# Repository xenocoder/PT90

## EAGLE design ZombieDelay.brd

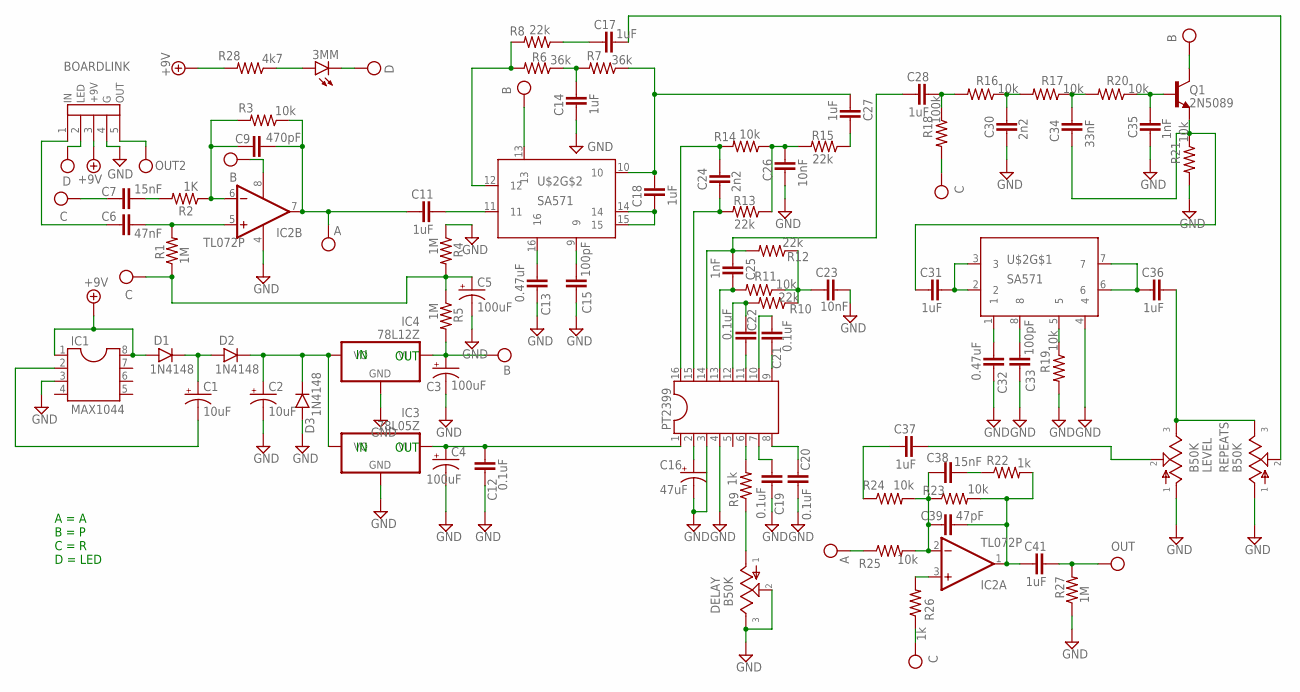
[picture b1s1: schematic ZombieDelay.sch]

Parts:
3MM: LED3MM
C1, C2: 10uF; 050_020_1
C3, C4, C5: 100uF; 080_035_1
C6: 47nF; 072X035
C7, C38: 15nF; 072X025
C9: 470pF; 050X030_025
C11, C14, C17, C18, C27, C28, C31, C36, C37, C41: 1uF; 072X045
C12, C19, C20, C21, C22: 0.1uF; 072X035
C13, C32: 0.47uF; 072X035
C15, C33: 100pF; 050X030_025
C16: 47uF; 063_025
C23, C26: 10nF; 072X025
C24, C30: 2n2; 072X025
C25, C35: 1nF; 072X025
C34: 33nF; 072X025
C39: 47pF; 050X030_025
D1, D2, D3: 1N4148; DO35-3
DELAY: B50K; 16MM_PCB_PADS
IC1: MAX1044; DIL08
IC2: TL072P; DIL08
IC3: 78L05Z; TO92
IC4: 78L12Z; TO92
LEVEL: B50K; 16MM_PCB_PADS
PT2399: DIL16
Q1: 2N5089; TO92-
R1, R4, R5, R27: 1M; R0207/3
R2: 1K; R0207/3
R3, R11, R14, R16, R17, R19, R20, R21, R23, R24, R25: 10k; R0207/3
R6, R7: 36k; R0207/3
R8, R10, R12, R13, R15: 22k; R0207/3
R9, R22, R26: 1k; R0207/3
R18: 100k; R0207/3
R28: 4k7; R0207/3
REPEATS: B50K; 16MM_PCB_PADS
U$1: BOARDLINK
U$2: SA571; DIL16

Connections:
+9V: D1.A, IC1.1, IC1.8, R28.2, U$1.3 (+9V)
A: C9.2, C11.1, IC2.7 (OUT), R3.1, R25.1
B: C3.+, IC2.8 (V+), IC4.1 (VI), Q1.1 (C), R5.2, U$2.13
C: C5.+, C7.1, R1.1, R4.2, R5.1, R18.2, R26.1
D: 3MM.K (C), U$1.2 (LED)
GND: C2.-, C3.-, C4.-, C5.-, C12.1, C13.2, C14.1, C15.1, C16.-, C19.2, C20.2, C23.2, C26.1, C30.1, C32.2, C33.1, C35.1, D3.A, DELAY.2, DELAY.3, IC1.3, IC2.4 (V-), IC3.2 (GND), IC4.2 (GND), LEVEL.1, PT2399.3, PT2399.4, R4.1, R19.2, R21.2, R27.1, REPEATS.1, U$1.4 (G), U$2.4
unnamed: C2.+, D2.C, D3.C, IC3.3 (VO), IC4.3 (VO)
unnamed: C1.+, D1.C, D2.A
unnamed: C1.-, IC1.2
unnamed: 3MM.A, R28.1
unnamed: C11.2, U$2.11
unnamed: C4.+, C12.2, IC3.1 (VI), PT2399.1
unnamed: C6.1, U$1.1 (IN)
unnamed: C6.2, IC2.5 (+IN), R1.2
unnamed: C7.2, R2.2
unnamed: C9.1, IC2.6 (-IN), R2.1, R3.2
unnamed: R6.2, R8.2, U$2.12
unnamed: C17.1, R8.1
unnamed: C14.2, R6.1, R7.2
unnamed: C18.1, U$2.14, U$2.15
unnamed: C18.2, C27.1, R7.1, U$2.10
unnamed: C13.1, U$2.16
unnamed: C15.2, U$2.9
unnamed: C16.+, PT2399.2
unnamed: PT2399.6, R9.2
unnamed: DELAY.1, R9.1
unnamed: C19.1, PT2399.7
unnamed: C20.1, PT2399.8
unnamed: C21.2, PT2399.9
unnamed: C21.1, PT2399.10
unnamed: C22.2, PT2399.11
unnamed: C22.1, PT2399.12, R10.2
unnamed: C23.1, R10.1, R11.1, R12.1
unnamed: C25.1, PT2399.13, R11.2
unnamed: C25.2, C28.1, PT2399.14, R12.2
unnamed: C24.2, PT2399.16, R14.2
unnamed: C24.1, PT2399.15, R13.2
unnamed: C27.2, R15.1
unnamed: C26.2, R13.1, R14.1, R15.2
unnamed: C31.2, U$2.2, U$2.3
unnamed: C28.2, R16.2, R18.1
unnamed: C30.2, R16.1, R17.2
unnamed: C34.2, R17.1, R20.2
unnamed: C35.2, Q1.2 (B), R20.1
unnamed: C31.1, C34.1, Q1.3 (E), R21.1
unnamed: C38.2, C39.2, IC2.2 (-IN), R23.1, R24.2, R25.2
unnamed: IC2.3 (+IN), R26.2
unnamed: C36.1, U$2.6, U$2.7
unnamed: C32.1, U$2.1
unnamed: C33.2, U$2.8
unnamed: R19.1, U$2.5
unnamed: C37.2, LEVEL.2
unnamed: C36.2, LEVEL.3, REPEATS.3
unnamed: C37.1, R24.1
unnamed: C38.1, R22.1
unnamed: C39.1, C41.1, IC2.1 (OUT), R22.2, R23.2
unnamed: C17.2, REPEATS.2
OUT: C41.2, R27.2, U$1.5 (OUT)

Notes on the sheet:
A = A B = P C = R D = LED
OUT

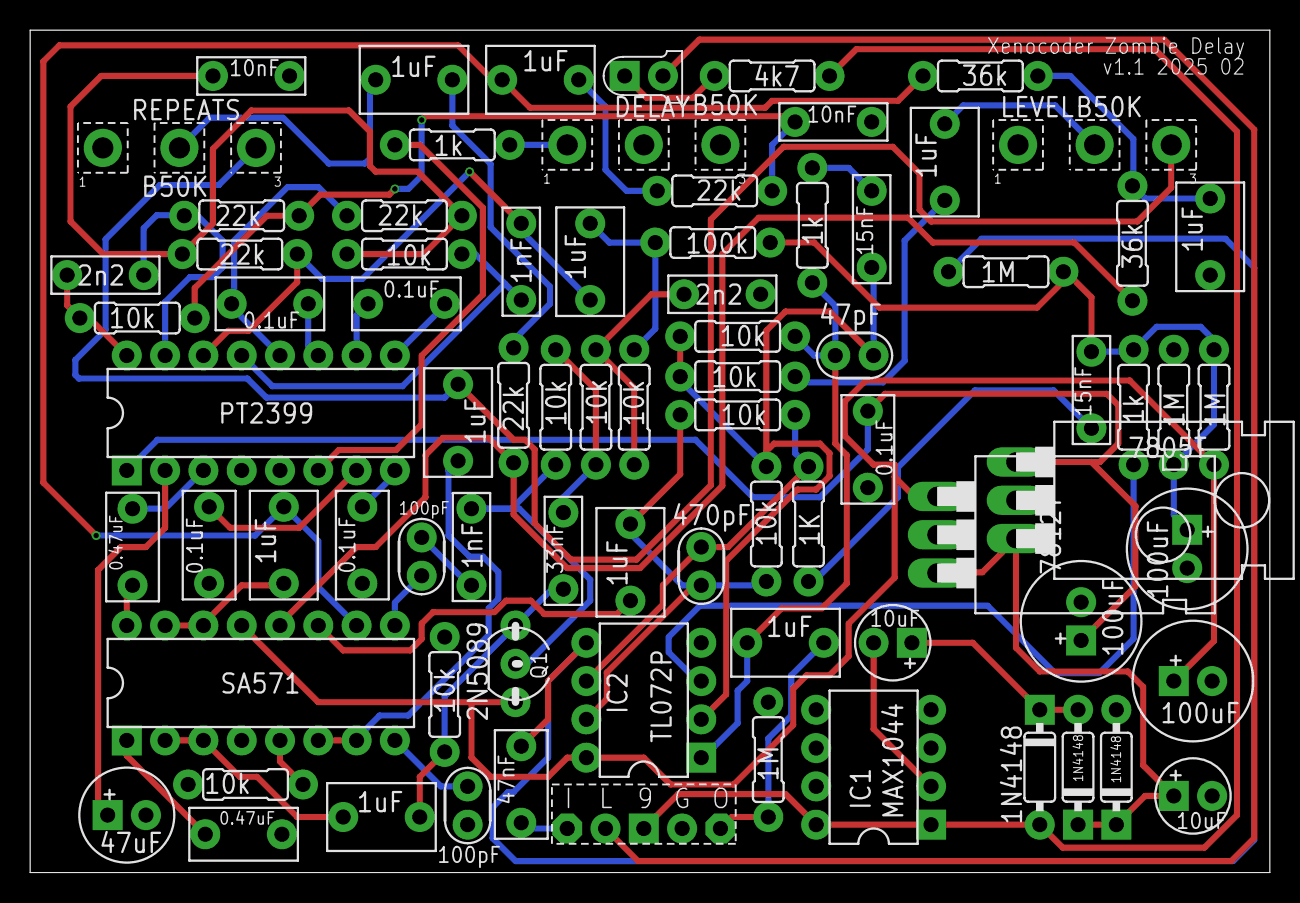
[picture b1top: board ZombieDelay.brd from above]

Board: 2 copper layers, 82.2 x 55.9 mm, 80 parts (0 on the bottom side), 58 nets.

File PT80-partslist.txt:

Partlist

Exported from PT80.brd at 1/18/20 4:56 PM

EAGLE Version 9.5.2 Copyright (c) 1988-2019 Autodesk, Inc.

Assembly variant: 

Part     Value          Package     Library         Position (mil)        Orientation

C1       10uF           050_020_1   mb_caps-electro (2150 600)            R180
C2       10uF           050_020_1   mb_caps-electro (2815 200)            R0
C3       100uF          080_035_1   mb_caps-electro (2800 500)            R0
C4       100uF          080_035_1   mb_caps-electro (2450 650)            R90
C5       100uF          080_035_1   mb_caps-electro (2785 845)            R270
C6       47nF           072X035     mb_caps-box     (1180 230)            R90
C7       15nF           072X025     mb_caps-box     (2535 1260)           R270
C9       470pF          050X030_025 mb_caps-ceramic (1650 800)            R270
C11      1uF            072X045     mb_caps-box     (1465 810)            R270
C12      0.1uF          072X035     mb_caps-box     (2085 1105)           R90
C13      0.47uF         072X035     mb_caps-box     (165 850)             R90
C14      1uF            072X045     mb_caps-box     (2845 1660)           R90
C15      100pF          050X030_025 mb_caps-ceramic (920 825)             R270
C16      47uF           063_025     mb_caps-electro (150 150)             R0
C17      1uF            072X045     mb_caps-box     (900 2070)            R180
C18      1uF            072X045     mb_caps-box     (560 855)             R90
C19      0.1uF          072X035     mb_caps-box     (365 855)             R270
C20      0.1uF          072X035     mb_caps-box     (765 855)             R270
C21      0.1uF          072X035     mb_caps-box     (880 1485)            R0
C22      0.1uF          072X035     mb_caps-box     (445 1485)            R0
C23      10nF           072X025     mb_caps-box     (475 2080)            R0
C24      2n2            072X025     mb_caps-box     (125 1980)            R270
C25      1nF            072X025     mb_caps-box     (1180 1595)           R90
C26      10nF           072X025     mb_caps-box     (1995 1960)           R180
C27      1uF            072X045     mb_caps-box     (1230 2070)           R0
C28      1uF            072X045     mb_caps-box     (1360 1595)           R90
C30      2n2            072X025     mb_caps-box     (1705 1510)           R180
C31      1uF            072X045     mb_caps-box     (815 145)             R180
C32      0.47uF         072X035     mb_caps-box     (455 100)             R0
C33      100pF          050X030_025 mb_caps-ceramic (1040 175)            R90
C34      33nF           072X025     mb_caps-box     (1290 840)            R90
C35      1nF            072X025     mb_caps-box     (1050 850)            R90
C36      1uF            072X045     mb_caps-box     (1015 1175)           R90
C37      1uF            072X045     mb_caps-box     (2280 1670)           R90
C38      15nF           072X025     mb_caps-box     (2095 1680)           R270
C39      47pF           050X030_025 mb_caps-ceramic (2050 1350)           R0
C41      1uF            072X045     mb_caps-box     (1870 600)            R0
D1       1N4148         DO35-3      mb_diodes       (2400 275)            R270
D2       1N4148         DO35-3      mb_diodes       (2500 275)            R90
D3       1N4148         DO35-3      mb_diodes       (2600 275)            R90
DELAY    B50K           16MM        mb_pots         (1500 1900)           R180
IC1      MAX1044        DIL08       mb_ics          (2100 275)            R90
IC2      TL072P         DIL08       mb_ics          (1500 450)            R90
IC3      78L05Z         TO92        mb_regulators   (2505 935)            R90
IC4      78L12Z         TO92        mb_regulators   (2290 935)            R90
LEVEL    B50K           16MM        mb_pots         (2500 1900)           R180
PT2399                  DIL16       mb_ics          (500 1200)            R0
Q1       2N5089         TO92-       mb_trans        (1165 545)            R270
R1       1M             R0207/3     mb_resistors    (2365 1325)           R270
R2       1K             R0207/3     mb_resistors    (1930 910)            R270
R3       10k            R0207/3     mb_resistors    (1745 1195)           R0
R4       1M             R0207/3     mb_resistors    (2750 1215)           R270
R5       1M             R0207/3     mb_resistors    (2855 1215)           R270
R6       36k            R0207/3     mb_resistors    (2605 1625)           R270
R7       36k            R0207/3     mb_resistors    (1810 2075)           R0
R8       22k            R0207/3     mb_resistors    (1160 1220)           R270
R9       1k             R0207/3     mb_resistors    (1000 1900)           R180
R10      22k            R0207/3     mb_resistors    (875 1715)            R180
R11      10k            R0207/3     mb_resistors    (875 1615)            R0
R12      22k            R0207/3     mb_resistors    (445 1615)            R0
R13      22k            R0207/3     mb_resistors    (450 1715)            R180
R14      10k            R0207/3     mb_resistors    (125 1610)            R90
R15      22k            R0207/3     mb_resistors    (1685 1780)           R0
R16      10k            R0207/3     mb_resistors    (1475 1215)           R90
R17      10k            R0207/3     mb_resistors    (1375 1215)           R90
R18      100k           R0207/3     mb_resistors    (1680 1645)           R0
R19      10k            R0207/3     mb_resistors    (460 230)             R180
R20      10k            R0207/3     mb_resistors    (1270 1215)           R90
R21      10k            R0207/3     mb_resistors    (980 465)             R90
R22      1k             R0207/3     mb_resistors    (1940 1690)           R270
R23      10k            R0207/3     mb_resistors    (1745 1400)           R0
R24      10k            R0207/3     mb_resistors    (1745 1295)           R180
R25      10k            R0207/3     mb_resistors    (1820 910)            R90
R26      1k             R0207/3     mb_resistors    (2645 1215)           R270
R27      1M             R0207/3     mb_resistors    (1825 295)            R270
REPEATS  B50K           16MM        mb_pots         (500 1900)            R180
U$1      BOARDLINK      BOARDLINK   xc_library      (1400 115)            R0
U$2      SA571          DIL16       xc_library      (500 495)             R0

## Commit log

2020-01-17 Version 1.0
2020-01-19 Added partlist and PCB image
2020-02-16 Version 1.1 - Fixed repeats direction and orientation of power regulators
2020-04-22 Making an offshoot pedal Zombie Delay with artwork by Tad Leger
2020-04-30 Some clean up
2021-10-18 New PBC and Board layout
2025-07-05 Updated to include larger regulators
2025-07-05 Updated Partslist
2025-07-05 Added Zombie PCB with new Regs
2025-07-05 Added new PCB with regs
